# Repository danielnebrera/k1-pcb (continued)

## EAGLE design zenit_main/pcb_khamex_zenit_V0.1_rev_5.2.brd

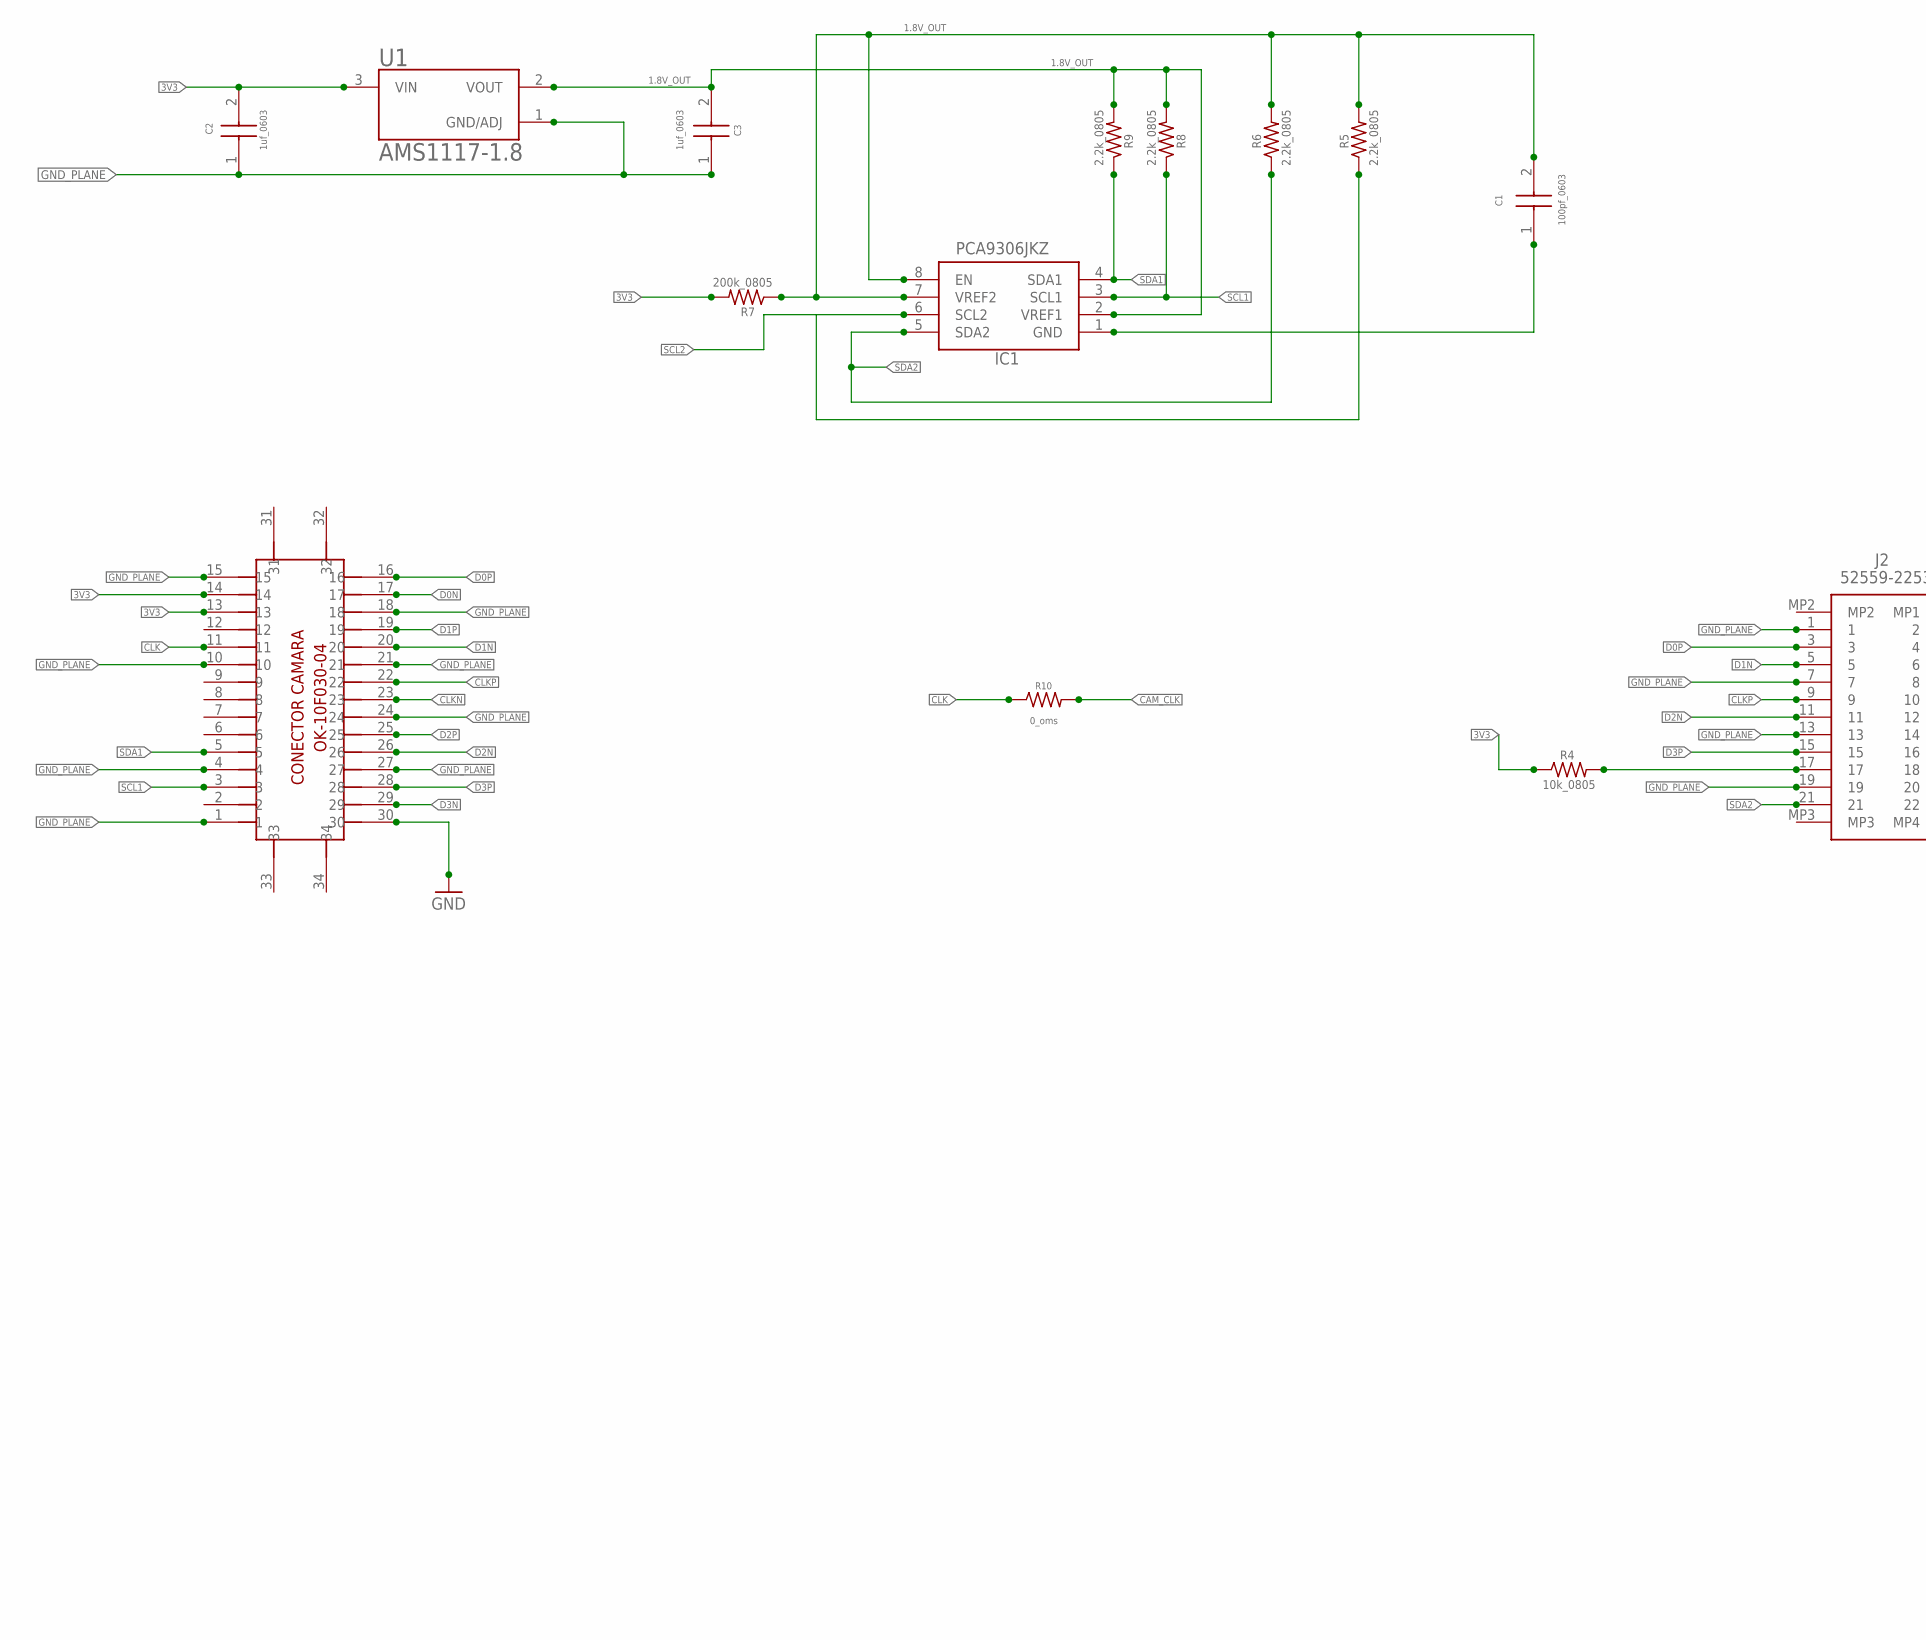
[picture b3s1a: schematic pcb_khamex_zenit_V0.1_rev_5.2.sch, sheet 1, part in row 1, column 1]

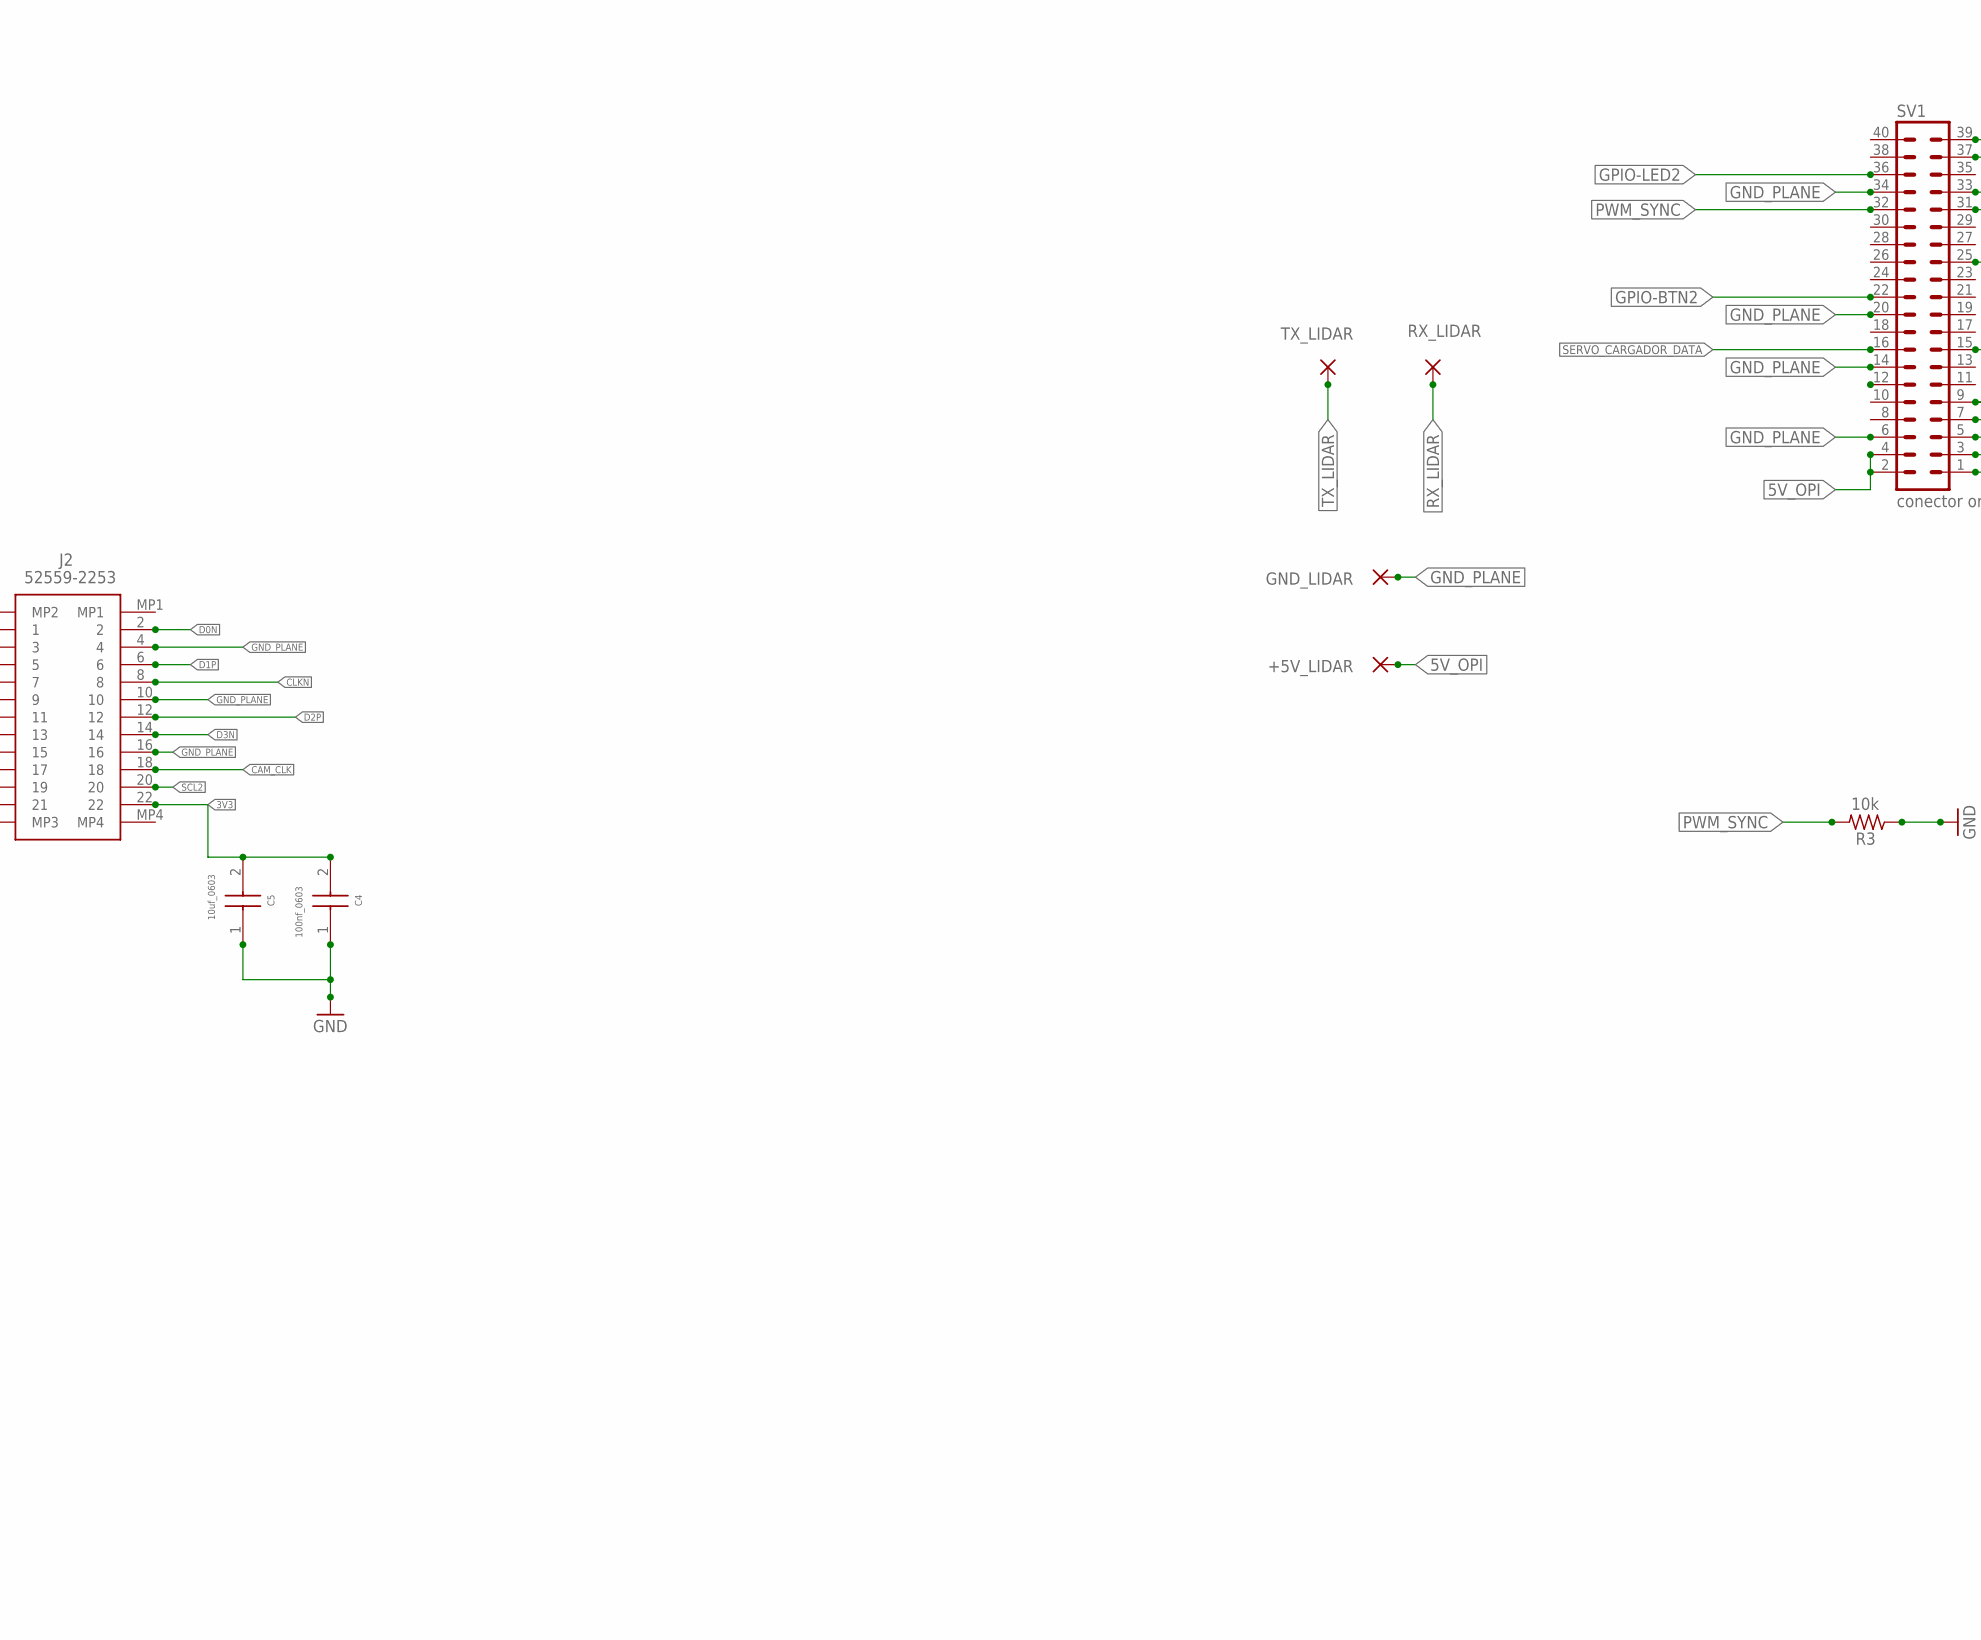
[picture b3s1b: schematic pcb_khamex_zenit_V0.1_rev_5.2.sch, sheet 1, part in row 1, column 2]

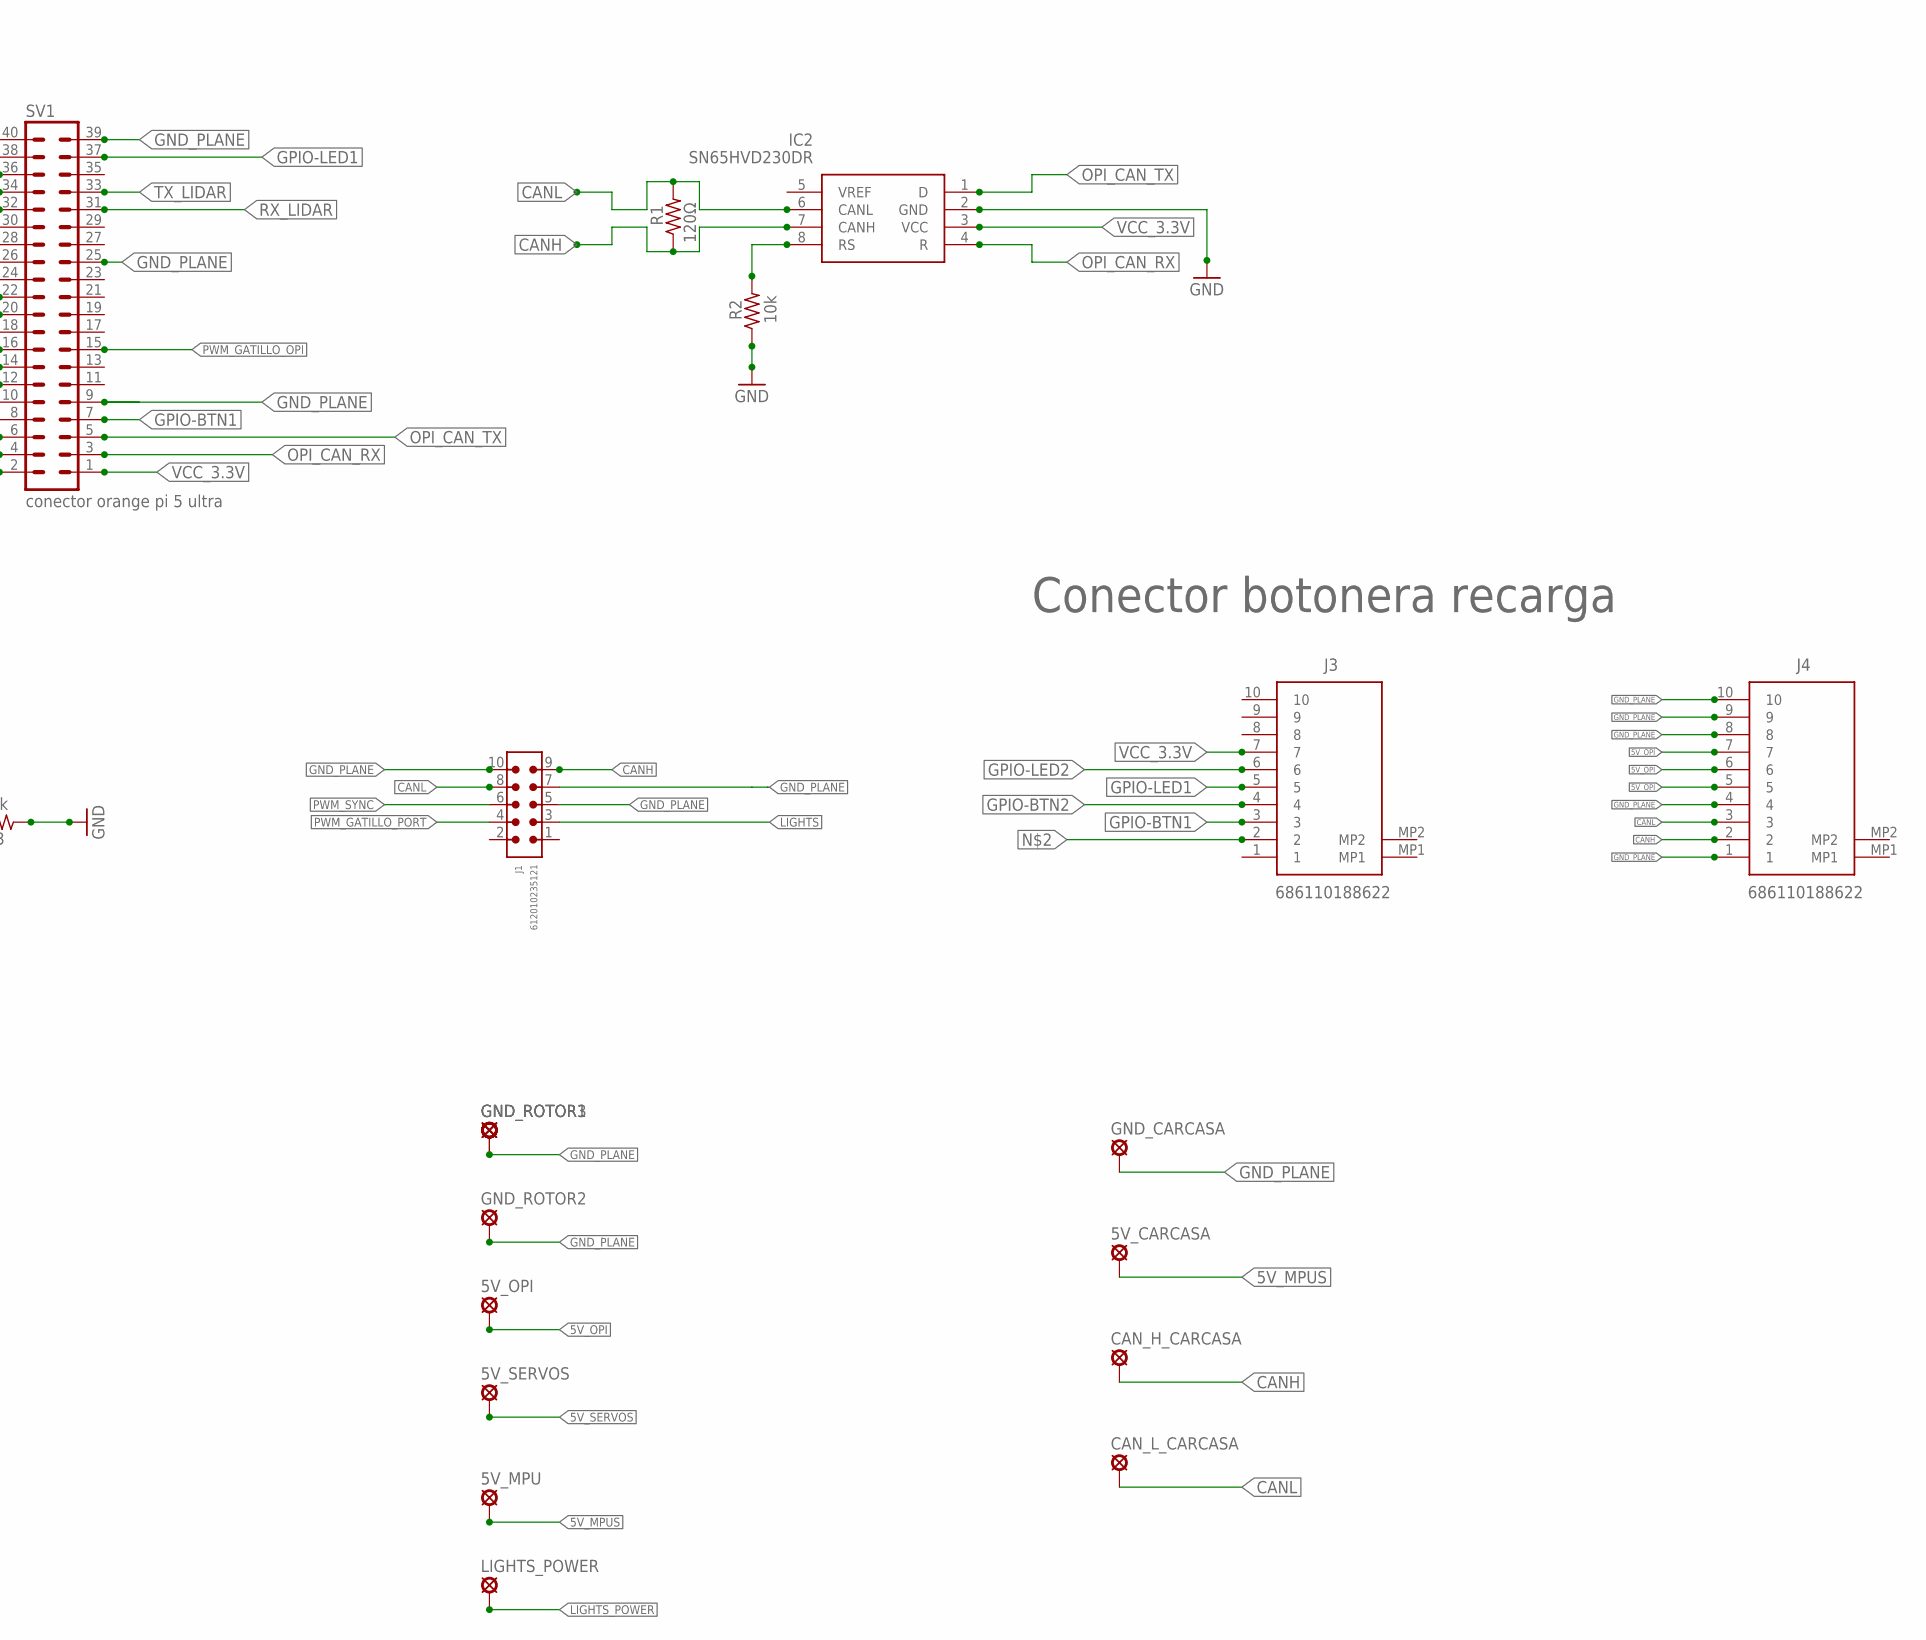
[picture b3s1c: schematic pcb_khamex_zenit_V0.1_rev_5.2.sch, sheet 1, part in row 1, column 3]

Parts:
5V_CARCASA, 5V_MPU, 5V_OPI, 5V_SERVOS: SE14
+5V_LIDAR: WIREPAD1,6/0,8; 1,6/0,8
C1: 100pf_0603; CAPC1608X90N
C2, C3: 1uf_0603; CAPC1608X90N
C4: 100nf_0603; CAPC1608X90N
C5: 10uf_0603; CAPC1608X90N
CAN_H_CARCASA: SE14
CAN_L_CARCASA: SE14
GND_CARCASA: SE14
GND_LIDAR: WIREPAD1,6/0,8; 1,6/0,8
GND_ROTOR1, GND_ROTOR2, GND_ROTOR3: SE14
IC1: PCA9306JKZ
IC2: SN65HVD230DR; SOT127P600X175-8N
J1: 612010235121
J2: 52559-2253; 525592253
J3, J4: 686110188622
LIGHTS_POWER: SE14
R1: 120Ω; M0805
R2: 10k; M0805
R3: 10k; R0603
R4: 10k_0805; M0805
R5, R6, R8, R9: 2.2k_0805; M0805
R7: 200k_0805; M0805
R10: 0_oms; M0805
RX_LIDAR: WIREPAD1,6/0,8; 1,6/0,8
SV1: conector orange pi 5 ultra; MA20-2
TX_LIDAR: WIREPAD1,6/0,8; 1,6/0,8
U1: AMS1117-1.8; SOT229P700X180-4N
U$1: OK-10F030-04_DEVICE; OK-10F030-04_PACKAGE

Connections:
1.8V: C3.2, IC1.2 (VREF1), R8.2, R9.2, U1.2 (VOUT)
3V3: C2.2, C4.2, C5.2, J2.22, R4.1, R7.2, U1.3 (VIN), U$1.13, U$1.14
5V_MPUS: 5V_CARCASA.MP, 5V_MPU.MP
5V_OPI: 5V_OPI.MP, +5V_LIDAR.1, J4.5, J4.6, J4.7, SV1.2, SV1.4
5V_SERVOS: 5V_SERVOS.MP; also elsewhere on the board
CAM_CLK: J2.18, R10.2
CANH: CAN_H_CARCASA.MP, IC2.7 (CANH), J1.9, J4.2, R1.1
CANL: CAN_L_CARCASA.MP, IC2.6 (CANL), J1.8, J4.3, R1.2
CLK: R10.1, U$1.11
CLKN: J2.8, U$1.23
CLKP: J2.9, U$1.22
D0N: J2.2, U$1.17
D0P: J2.3, U$1.16
D1N: J2.5, U$1.20
D1P: J2.6, U$1.19
D2N: J2.11, U$1.26
D2P: J2.12, U$1.25
D3N: J2.14, U$1.29
D3P: J2.15, U$1.28
GND_PLANE: C2.1, C3.1, C4.1, C5.1, GND_CARCASA.MP, GND_LIDAR.1, GND_ROTOR1.MP, GND_ROTOR2.MP, GND_ROTOR3.MP, IC2.2 (GND), J1.5, J1.7, J1.10, J2.1, J2.4, J2.7, J2.10, J2.13, J2.16, J2.19, J4.1, J4.4, J4.8, J4.9, J4.10, R2.1, R3.1, SV1.6, SV1.9, SV1.14, SV1.20, SV1.25, SV1.34, SV1.39, U1.1 (GND/ADJ), U$1.1, U$1.4, U$1.10, U$1.15, U$1.18, U$1.21, U$1.24, U$1.27, U$1.30; also elsewhere on the board
GPIO-BTN1: J3.3, SV1.7
GPIO-BTN2: J3.4, SV1.22
GPIO-LED1: J3.5, SV1.37
GPIO-LED2: J3.6, SV1.36
LIGHTS: J1.3
LIGHTS_POWER: LIGHTS_POWER.MP
unnamed: C1.1, IC1.1 (GND)
unnamed: C1.2, IC1.7 (VREF2), IC1.8 (EN), R5.2, R6.2, R7.1
unnamed: J2.17, R4.2
unnamed: IC2.8 (RS), R2.2
OPI_CAN_RX: IC2.4 (R), SV1.3
OPI_CAN_TX: IC2.1 (D), SV1.5
PWM_GATILLO_OPI: SV1.15; also elsewhere on the board
PWM_GATILLO_PORT: J1.4; also elsewhere on the board
PWM_SYNC: J1.6, R3.2, SV1.32
RX_LIDAR: RX_LIDAR.1, SV1.31
SCL1: IC1.3 (SCL1), R8.1, U$1.3
SCL2: IC1.6 (SCL2), J2.20, R5.1
SDA1: IC1.4 (SDA1), R9.1, U$1.5
SDA2: IC1.5 (SDA2), J2.21, R6.1
SERVO_CARGADOR_DATA: SV1.16; also elsewhere on the board
TX_LIDAR: SV1.33, TX_LIDAR.1
VCC_3.3V: IC2.3 (VCC), J3.7, SV1.1

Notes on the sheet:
Conector botonera recarga
1.8V_OUT

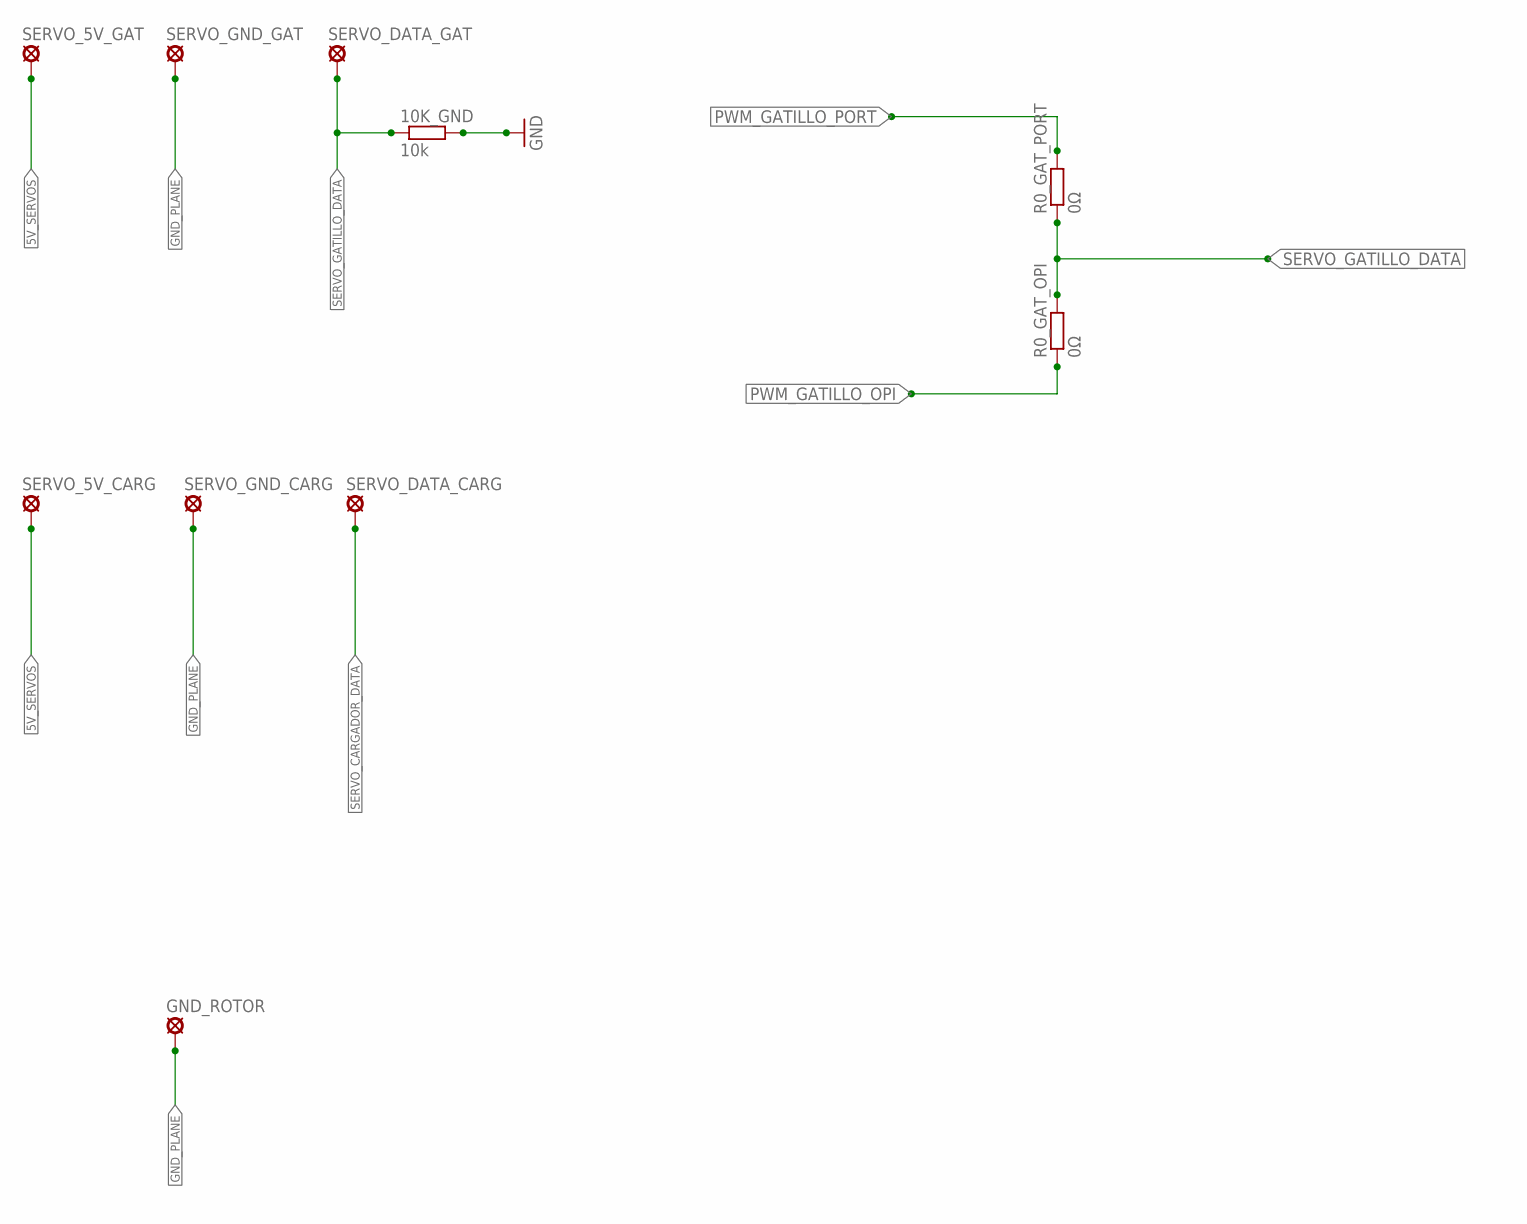
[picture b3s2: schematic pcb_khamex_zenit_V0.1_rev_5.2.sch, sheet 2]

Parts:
10K_GND: 10k; R0603
GND_ROTOR: SE14
R0_GAT_OPI, R0_GAT_PORT: 0Ω; R0603
SERVO_5V_CARG, SERVO_5V_GAT: SE14
SERVO_DATA_CARG: SE14
SERVO_DATA_GAT: SE14
SERVO_GND_CARG: SE14
SERVO_GND_GAT: SE14

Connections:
5V_SERVOS: SERVO_5V_CARG.MP, SERVO_5V_GAT.MP; also elsewhere on the board
GND_PLANE: 10K_GND.2, GND_ROTOR.MP, SERVO_GND_CARG.MP, SERVO_GND_GAT.MP; also elsewhere on the board
PWM_GATILLO_OPI: R0_GAT_OPI.1; also elsewhere on the board
PWM_GATILLO_PORT: R0_GAT_PORT.2; also elsewhere on the board
SERVO_CARGADOR_DATA: SERVO_DATA_CARG.MP; also elsewhere on the board
SERVO_GATILLO_DATA: 10K_GND.1, R0_GAT_OPI.2, R0_GAT_PORT.1, SERVO_DATA_GAT.MP

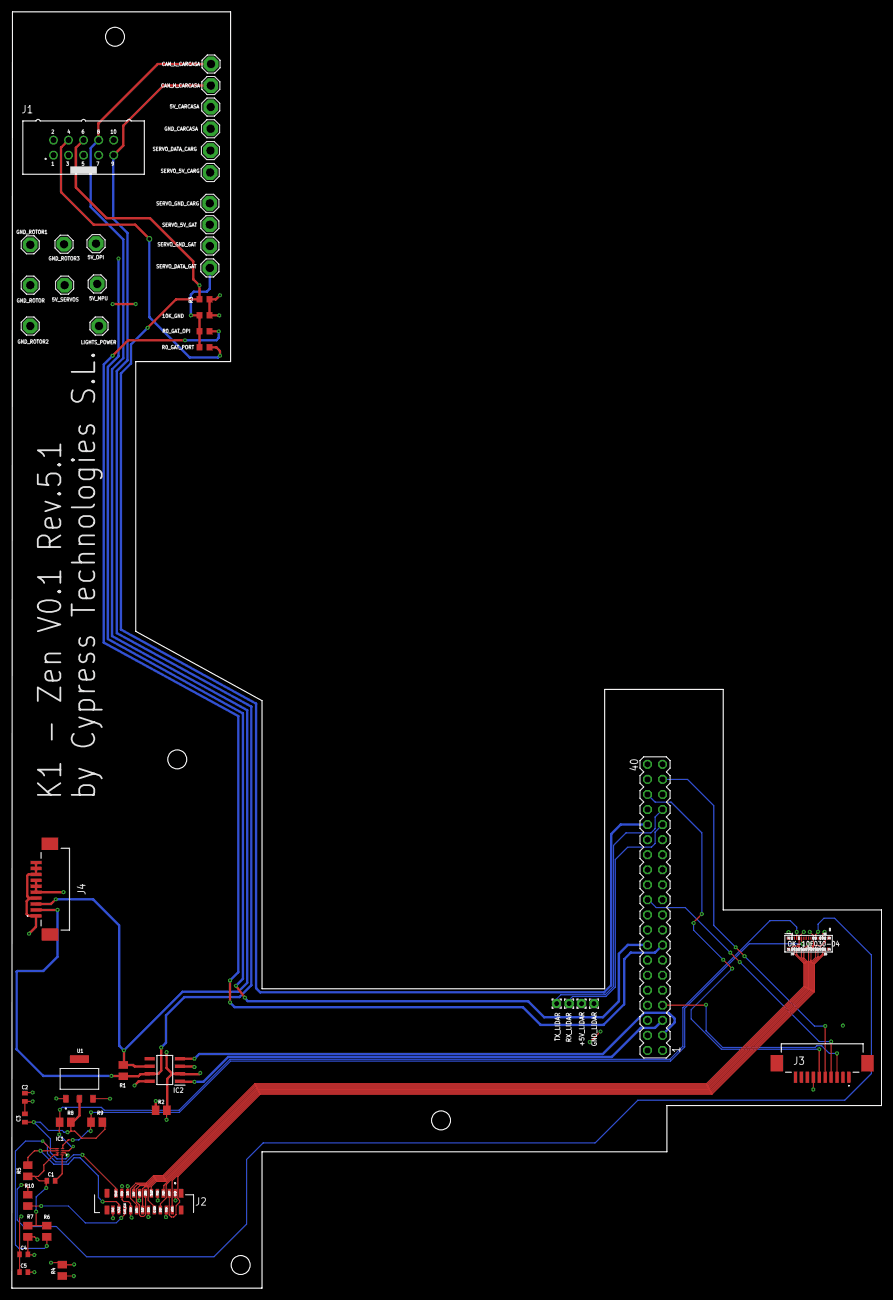
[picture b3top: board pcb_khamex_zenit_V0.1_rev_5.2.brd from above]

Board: 4 copper layers, 146.7 x 215.3 mm, 49 parts (0 on the bottom side), 42 nets.

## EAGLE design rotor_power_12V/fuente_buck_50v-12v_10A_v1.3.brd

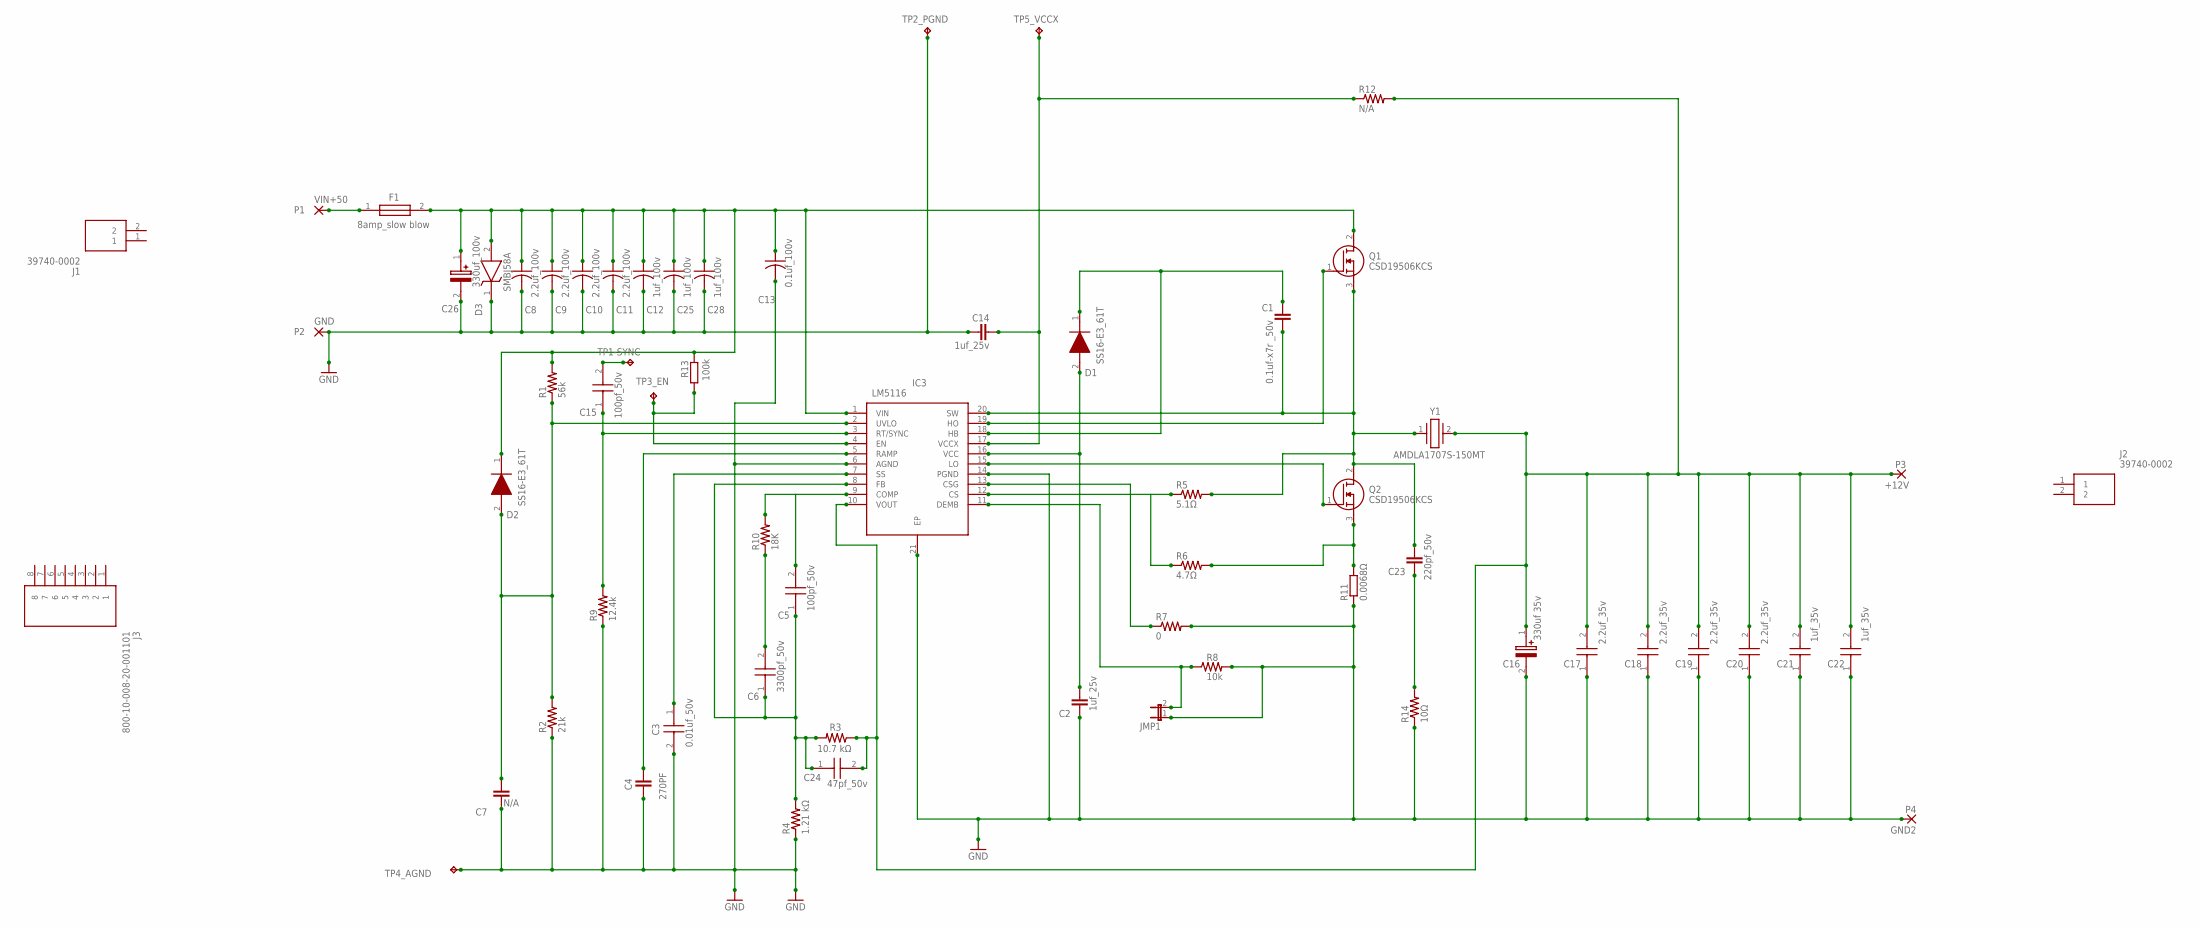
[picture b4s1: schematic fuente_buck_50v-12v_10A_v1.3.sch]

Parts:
+12V: P3; 2,54/1,1
C1: 0.1uf-x7r _50v; C0805
C2, C14: 1uf_25v; C0805
C3: 0.01uf_50v; CAPC1608X90N
C4: 270PF; C0805
C5, C15: 100pf_50v; CAPC1608X90N
C6: 3300pf_50v; CAPC1608X90N
C7: N/A; C0805
C8, C9, C10, C11: 2.2uf_100v; C1206
C12, C25, C28: 1uf_100v; C1206
C13: 0.1uf_100v; C1206
C16: 330uf 35v; EEE0JA152UAP
C17, C18, C19, C20: 2.2uf_35v; CAPC3216X180N
C21, C22: 1uf_35v; CAPC3216X180N
C23: 220pf_50v; C0805
C24: 47pf_50v; CAPC1608X90N
C26: 330uf_100v; CAPAE1910X1750N
D1, D2: SS16-E3_61T; DIOM5127X229N
D3: SMBJ58A; DIOM5436X261N
F1: 8amp_slow blow; FUSC3216X123N
GND: P2; 2,54/1,1
GND2: P4; 2,54/1,1
IC3: LM5116; SOP65P640X110-21N
J1, J2: 39740-0002; 397400002
J3: 800-10-008-20-001101; HDRRA8W60P0X254_1X8_2032X295X2
JMP1: JP1E; JP1
Q1, Q2: CSD19506KCS; TO254P470X1016X1611-3P
R1: 56k; M0805
R2: 21k; M0805
R3: 10.7 kΩ; M0805
R4: 1.21 kΩ; M0805
R5: 5.1Ω; M0805
R6: 4.7Ω; M0805
R7: 0; M0805
R8: 10k; M0805
R9: 12.4k; M0805
R10: 18K; M0805
R11: 0.0068Ω; R2512
R12: N/A; M0805
R13: 100k; R0805
R14: 10Ω; M0805
TP1-SYNC: TP1; P1-13
TP2_PGND, TP3_EN, TP4_AGND, TP5_VCCX: TPPAD1-13; P1-13
VIN+50: P1; 2,54/1,1
Y1: AMDLA1707S-150MT; INDPM178169X700N

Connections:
10K: C2.1, D1.2 (A), IC3.16 (VCC)
GND: C2.2, C3.2, C4.2, C7.2, C8.2, C9.2, C10.2, C11.2, C12.2, C13.2, C14.1, C16.2 (-), C17.1, C18.1, C19.1, C20.1, C21.1, C22.1, C25.2, C26.2 (-), C28.2, D3.1 (K), GND.1, GND2.1, IC3.6 (AGND), IC3.14 (PGND), IC3.21 (EP), JMP1.1, R2.1, R4.1, R7.2, R8.2, R9.1, R11.1, R14.1, TP2_PGND.TP, TP4_AGND.TP
unnamed: C5.1, C6.1, C24.1, IC3.8 (FB), R3.2, R4.2
unnamed: F1.1, VIN+50.1
unnamed: C23.2, R14.2
unnamed: C7.1, D2.2 (A), IC3.2 (UVLO), R1.1, R2.2
unnamed: C15.1, IC3.3 (RT/SYNC), R9.2
unnamed: C15.2, TP1-SYNC.TP
unnamed: C4.1, IC3.5 (RAMP)
unnamed: C3.1, IC3.7 (SS)
unnamed: C14.2, IC3.17 (VCCX), R12.1, TP5_VCCX.TP
unnamed: C5.2, IC3.9 (COMP), R10.2
unnamed: IC3.19 (HO), Q1.1 (G)
unnamed: C6.2, R10.1
unnamed: +12V.1, C16.1 (+), C17.2, C18.2, C19.2, C20.2, C21.2, C22.2, C24.2, IC3.10 (VOUT), R3.1, R12.2, Y1.2
unnamed: IC3.4 (EN), R13.1, TP3_EN.TP
unnamed: C1.1, C23.1, IC3.20 (SW), Q1.3 (S), Q2.2 (D), R5.2, Y1.1
unnamed: IC3.15 (LO), Q2.1 (G)
unnamed: C1.2, D1.1 (K), IC3.18 (HB)
unnamed: IC3.13 (CSG), R7.1
unnamed: Q2.3 (S), R6.2, R11.2
unnamed: IC3.11 (DEMB), JMP1.2, R8.1
unnamed: IC3.12 (CS), R5.1, R6.1
VIN: C8.1, C9.1, C10.1, C11.1, C12.1, C13.1, C25.1, C26.1 (+), C28.1, D2.1 (K), D3.2 (A), F1.2, IC3.1 (VIN), Q1.2 (D), R1.2, R13.2

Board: 2 copper layers, 62 parts (1 on the bottom side), 24 nets, no tracks yet.

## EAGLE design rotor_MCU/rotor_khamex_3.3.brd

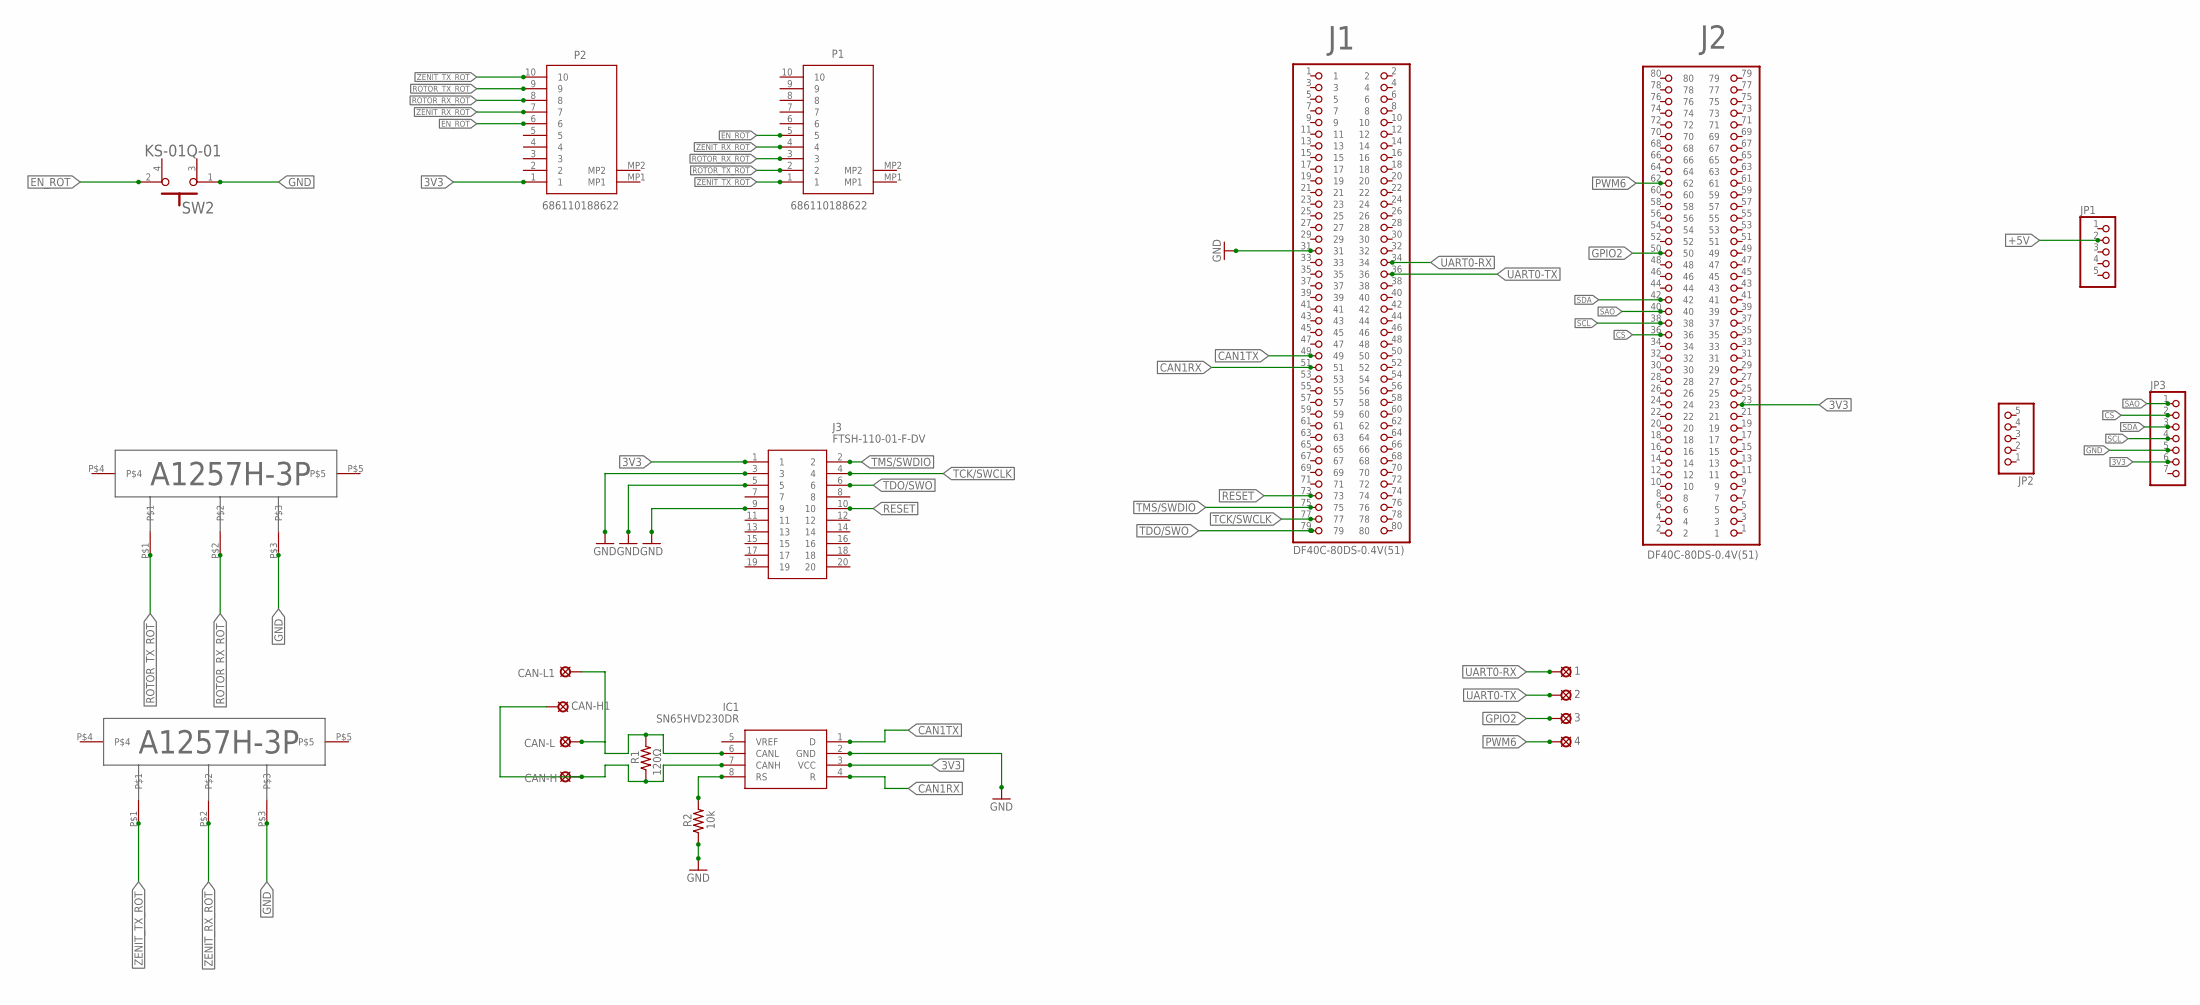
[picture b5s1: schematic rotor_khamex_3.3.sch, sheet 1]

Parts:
1, 2, 3, 4: LSP11
CAN-H, CAN-H1: LSP11
CAN-L, CAN-L1: LSP11
IC1: SN65HVD230DR; SOT127P600X175-8N
J1, J2: DF40C-80DS-0.4V(51); HRS_DF40C-80DS-0.4V(51)
J3: FTSH-110-01-F-DV; FTSH-110-XX-YYY-DV
JP1, JP2: PINHD-1X5; 1X05
JP3: PINHD-1X7; 1X07
MOTOR_ROTOR: A1257H-3P_DEVICE; A1257H-3P_PACK
MOTOR_ZENIT: A1257H-3P_DEVICE; A1257H-3P_PACK
P1, P2: 686110188622
R1: 120Ω; M0805
R2: 10k; M0805
SW2: E-SWITCH_KS-01Q-01E-SWITCH_KS-01Q-01_0_0; E-SWITCH_KS-01Q-01_0

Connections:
3V3: IC1.3 (VCC), J2.23, J3.1, JP3.6, P2.1
+5V: JP1.2; also elsewhere on the board
CAN1RX: IC1.4 (R), J1.51
CAN1TX: IC1.1 (D), J1.49
CS: J2.36, JP3.2
EN_ROT: P1.5, P2.6, SW2.2
GND: IC1.2 (GND), J1.31, J3.3, J3.5, J3.9, JP3.5, MOTOR_ROTOR.P$3, MOTOR_ZENIT.P$3, R2.1, SW2.1; also elsewhere on the board
GPIO2: 3.MP, J2.50
unnamed: CAN-H.MP, CAN-H1.MP, IC1.7 (CANH), R1.1
unnamed: CAN-L.MP, CAN-L1.MP, IC1.6 (CANL), R1.2
unnamed: IC1.8 (RS), R2.2
PWM6: 4.MP, J2.62
RESET: J1.73, J3.10
ROTOR_RX_ROT: MOTOR_ROTOR.P$2, P1.3, P2.8
ROTOR_TX_ROT: MOTOR_ROTOR.P$1, P1.2, P2.9
SAO: J2.40, JP3.1
SCL: J2.38, JP3.4
SDA: J2.42, JP3.3
TCK/SWCLK: J1.77, J3.4
TDO/SWO: J1.79, J3.6
TMS/SWDIO: J1.75, J3.2
UART0-RX: 1.MP, J1.34
UART0-TX: 2.MP, J1.36
ZENIT_RX_ROT: MOTOR_ZENIT.P$2, P1.4, P2.7
ZENIT_TX_ROT: MOTOR_ZENIT.P$1, P1.1, P2.10

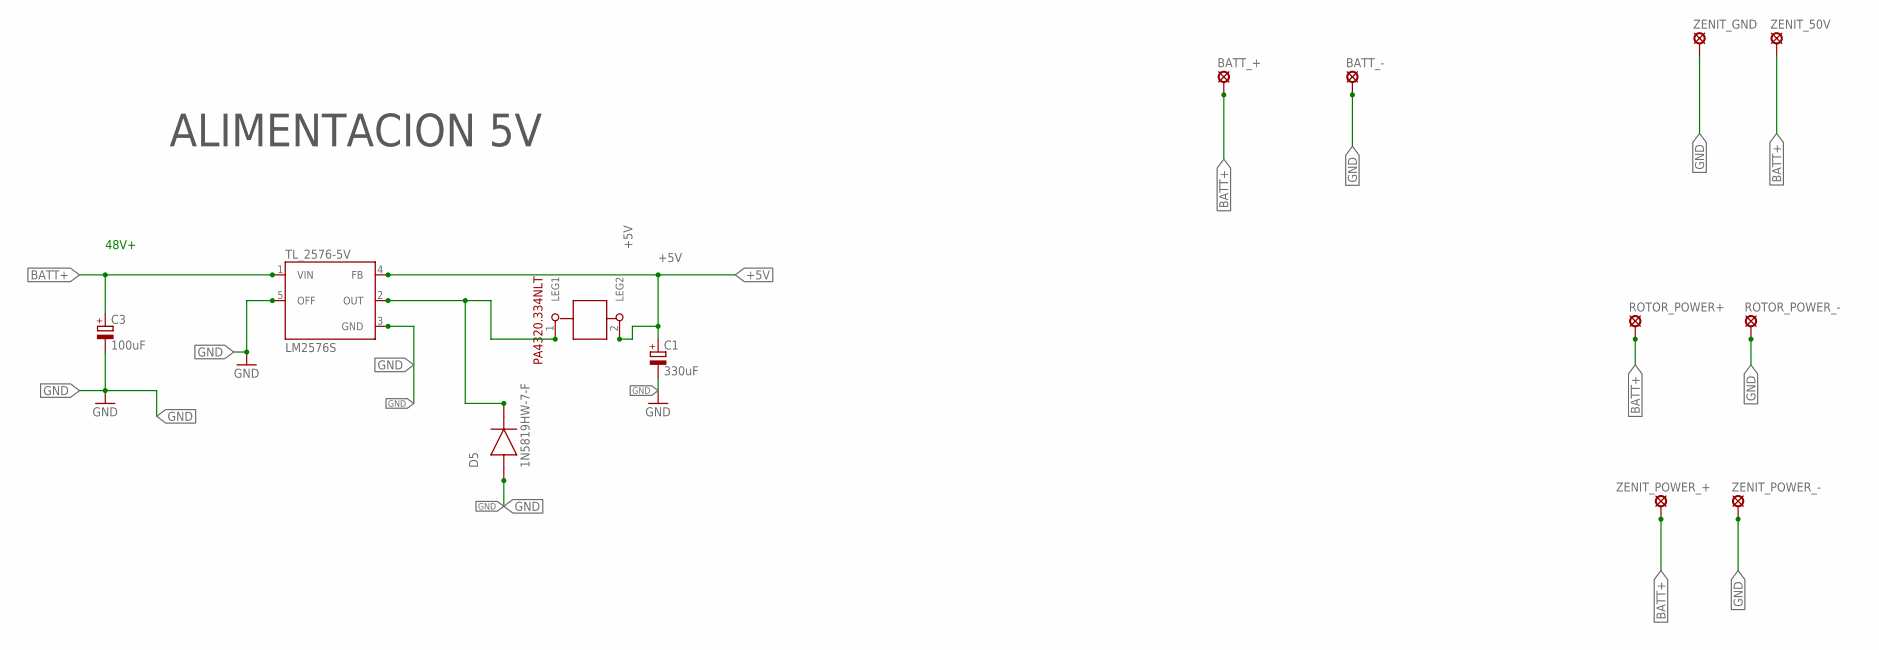
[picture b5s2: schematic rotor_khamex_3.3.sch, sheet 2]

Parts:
BATT_+: SE14
BATT_-: SE14
C1: 330uF; E5-10,5
C3: 100uF; E5-10,5
D5: 1N5819HW-7-F; SOD370155X135
L: 1212; 1212SMDINDUCTORPACK
ROTOR_POWER+: SE14
ROTOR_POWER_-: SE14
TL_2576-5V: LM2576S; TO263-5
ZENIT_50V: SE14
ZENIT_GND: SE14
ZENIT_POWER_+: SE14
ZENIT_POWER_-: SE14

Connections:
+5V: C1.+, L.2 (LEG2), TL_2576-5V.4 (FB); also elsewhere on the board
BATT+: BATT_+.MP, C3.+, ROTOR_POWER+.MP, TL_2576-5V.1 (VIN), ZENIT_50V.MP, ZENIT_POWER_+.MP
GND: BATT_-.MP, C1.-, C3.-, D5.2 (A), ROTOR_POWER_-.MP, TL_2576-5V.3 (GND), TL_2576-5V.5 (OFF), ZENIT_GND.MP, ZENIT_POWER_-.MP; also elsewhere on the board
unnamed: D5.1 (C), L.1 (LEG1), TL_2576-5V.2 (OUT)

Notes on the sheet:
48V+
ALIMENTACION 5V
